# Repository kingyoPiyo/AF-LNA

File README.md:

# AF-LNA
ADA4522-2ARMZ を 4パラで使用した低周波用のローノイズアンプです。  
帯域は 0.1～1000Hz、ゲインは 60dB、ノイズは 5nV/√Hz 以下となるように設計しています。  
⇒ 実測で 3.2nV/√Hz 程度となりました

## 主な仕様
| 項目 | 仕様 |
| ---- | ---- |
| 電源電圧 | 5V±0.5V（USB-C端子より供給） |
| 消費電流 | 50mA 以下 |
| 電圧利得 | 60dB（1000倍） |
| 電圧利得周波数特性 | 0.1～1000Hz（-3dB） |
| 入力換算雑音電圧密度 | 3.2nV/√Hz（typ） at 100Hz |
| 入力電圧範囲 | 入力保護クランプ ±0.5Vpp、DC 重畳は +30V 以下 |
| 入力結合 | AC結合（220uF、有極性コンデンサによる） |
| 入力インピーダンス | 10kΩ at 10～1000Hz |
| 出力インピーダンス | 120Ω at 10～1000Hz |
| 電源構成 | USB-C 側と回路の GND を絶縁型 DCDC により絶縁<br>（絶縁抵抗 100MΩ 以上 at DC500V） |
| 表示LED | 通電表示（D7：緑色）、出力クリッピング表示（D6：赤色） |

## PCB Image  

## Schematic
[Schematic.pdf](doc/schematic.pdf "Schematic")

## 開発環境
- KiCad Version 6.0.5

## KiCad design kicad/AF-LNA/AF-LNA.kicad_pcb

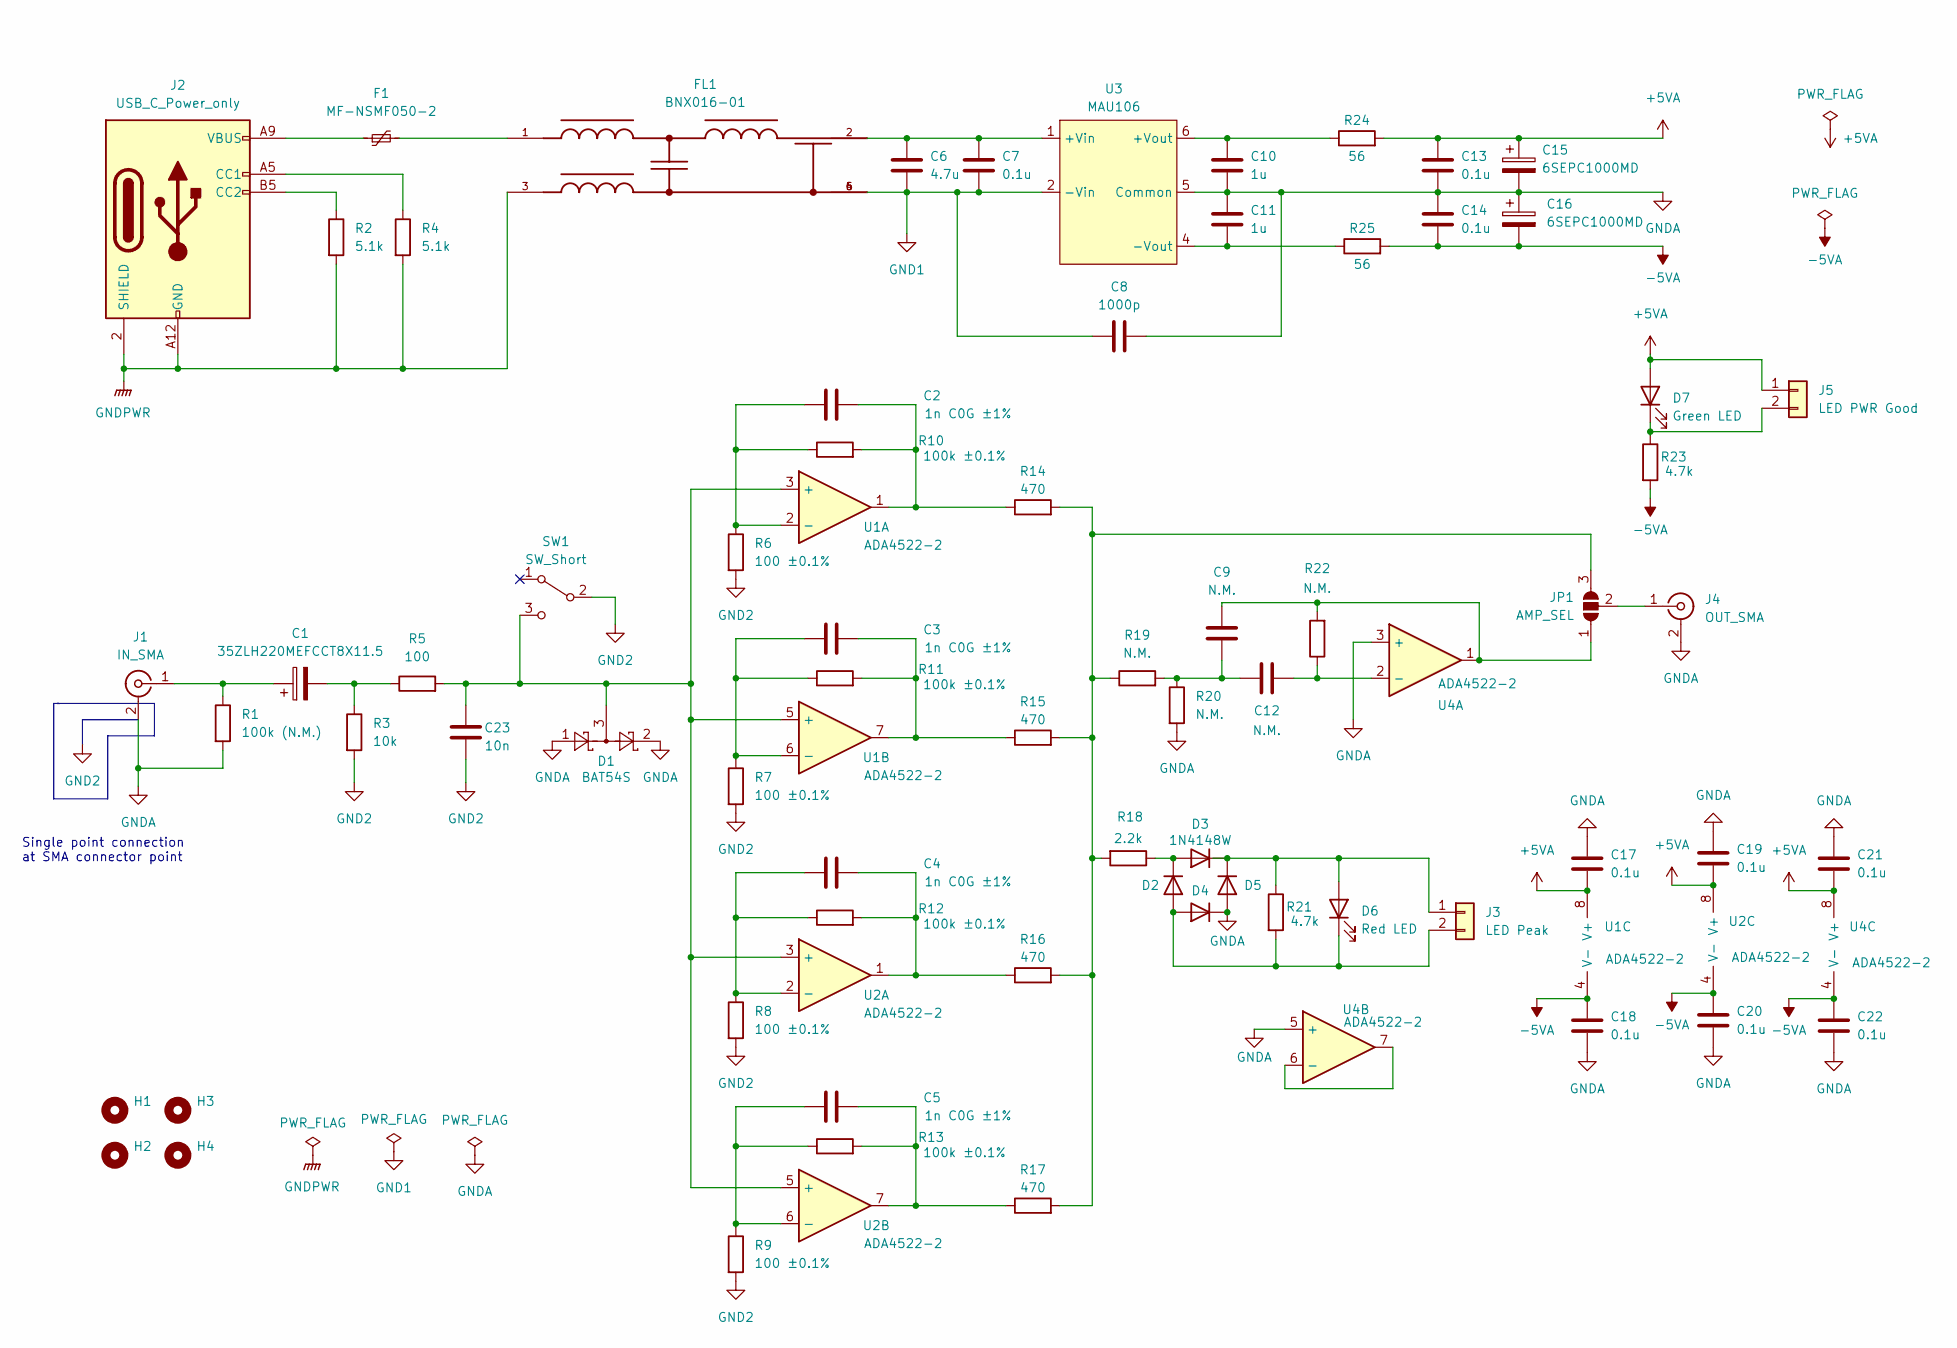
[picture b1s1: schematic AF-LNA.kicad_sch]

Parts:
C1: 35ZLH220MEFCCT8X11.5; CP_Radial_D8.0mm_P3.50mm
C2, C3, C4, C5: 1n C0G ±1%; C_0402_1005Metric
C6: 4.7u; C_0603_1608Metric
C7, C13, C14, C17, C18, C19, C20, C21, C22: 0.1u; C_0603_1608Metric
C8: 1000p; C_1812_4532Metric
C9, C12: N.M.; C_0603_1608Metric
C10, C11: 1u; C_0603_1608Metric
C15, C16: 6SEPC1000MD; CP_Radial_D8.0mm_P3.50mm
C23: 10n; C_0603_1608Metric
D1: BAT54S; SOT-523
D2, D3, D4, D5: 1N4148W; D_SOD-123
D6: Red LED; LED_0603_1608Metric
D7: Green LED; LED_0603_1608Metric
F1: MF-NSMF050-2; Fuse_1206_3216Metric
FL1: BNX016-01; FIL_BNX016-01
H1, H2, H3, H4: MountingHole; MountingHole_3.2mm_M3
J1: IN_SMA; S-063-49-TGG
J2: USB_C_Power_only; USB-C_Power_only
J3: LED Peak; PinHeader_1x02_P2.54mm_Vertical
J4: OUT_SMA; S-063-49-TGG
J5: LED PWR Good; PinHeader_1x02_P2.54mm_Vertical
JP1: AMP_SEL; SolderJumper-3_P1.3mm_Open_RoundedPad1.0x1.5mm
R1: 100k (N.M.); R_0603_1608Metric
R2, R4: 5.1k; R_0603_1608Metric
R3: 10k; R_0603_1608Metric
R5: 100; R_0603_1608Metric
R6, R7, R8, R9: 100 ±0.1%; R_0603_1608Metric
R10, R11, R12, R13: 100k ±0.1%; R_0603_1608Metric
R14, R15, R16, R17: 470; R_0603_1608Metric
R18: 2.2k; R_0603_1608Metric
R19, R20, R22: N.M.; R_0603_1608Metric
R21, R23: 4.7k; R_0603_1608Metric
R24, R25: 56; R_0603_1608Metric
SW1: SW_Short; 2MS1-T1-B4-VS2-Q-E-S
U1, U2, U4: ADA4522-2; MSOP-8_3x3mm_P0.65mm
U3: MAU106

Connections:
+5VA: C13.1, C15.1, C17.2, C19.2, C21.2, D7.2 (A), J5.1, R24.2, U1.8 (V+), U2.8 (V+), U4.8 (V+)
-5VA: C14.2, C16.2, C18.1, C20.1, C22.1, R23.2, R25.2, U1.4 (V-), U2.4 (V-), U4.4 (V-)
GND1: C6.2, C7.2, C8.1, FL1.4, FL1.5, FL1.6, U3.2 (-Vin)
GND2: C23.1, R3.2, R6.2, R7.2, R8.2, R9.2, SW1.2 (B)
GNDA: C8.2, C10.2, C11.1, C13.2, C14.1, C15.2, C16.1, C17.1, C18.2, C19.1, C20.2, C21.1, C22.2, D1.1, D1.2, D4.1 (K), D5.2 (A), J1.2 (Ext), J4.2 (Ext), R1.2, R20.2, U3.5 (Common), U4.3 (+), U4.5 (+)
GNDPWR: FL1.3, J2.2 (SHIELD), J2.A12 (GND), J2.B12 (GND), R2.2, R4.2
unnamed: C1.1, J1.1 (In), R1.1
unnamed: C1.2, R3.1, R5.1
unnamed: C2.1, R6.1, R10.1, U1.2 (-)
unnamed: C2.2, R10.2, R14.1, U1.1
unnamed: C3.1, R7.1, R11.1, U1.6 (-)
unnamed: C3.2, R11.2, R15.1, U1.7
unnamed: C4.1, R8.1, R12.1, U2.2 (-)
unnamed: C4.2, R12.2, R16.1, U2.1
unnamed: C5.1, R9.1, R13.1, U2.6 (-)
unnamed: C5.2, R13.2, R17.1, U2.7
unnamed: C6.1, C7.1, FL1.2, U3.1 (+Vin)
unnamed: C9.1, JP1.1 (A), R22.2, U4.1
unnamed: C10.1, R24.1, U3.6 (+Vout)
unnamed: C11.2, R25.1, U3.4 (-Vout)
unnamed: C9.2, C12.1, R19.2, R20.1
unnamed: C12.2, R22.1, U4.2 (-)
unnamed: D2.1 (K), D3.2 (A), R18.1
unnamed: D2.2 (A), D4.2 (A), D6.1 (K), J3.2, R21.2
unnamed: D3.1 (K), D5.1 (K), D6.2 (A), J3.1, R21.1
unnamed: F1.1, J2.A9 (VBUS), J2.B9 (VBUS)
unnamed: F1.2, FL1.1
unnamed: J2.A5 (CC1), R4.1
unnamed: J2.B5 (CC2), R2.1
unnamed: J4.1 (In), JP1.2 (C)
unnamed: D7.1 (K), J5.2, R23.1
unnamed: JP1.3 (B), R14.2, R15.2, R16.2, R17.2, R18.2, R19.1
unnamed: C23.2, D1.3, R5.2, SW1.3 (C), U1.3 (+), U1.5 (+), U2.3 (+), U2.5 (+)
unnamed: U4.6 (-), U4.7

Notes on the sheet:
Single point connection at SMA connector point

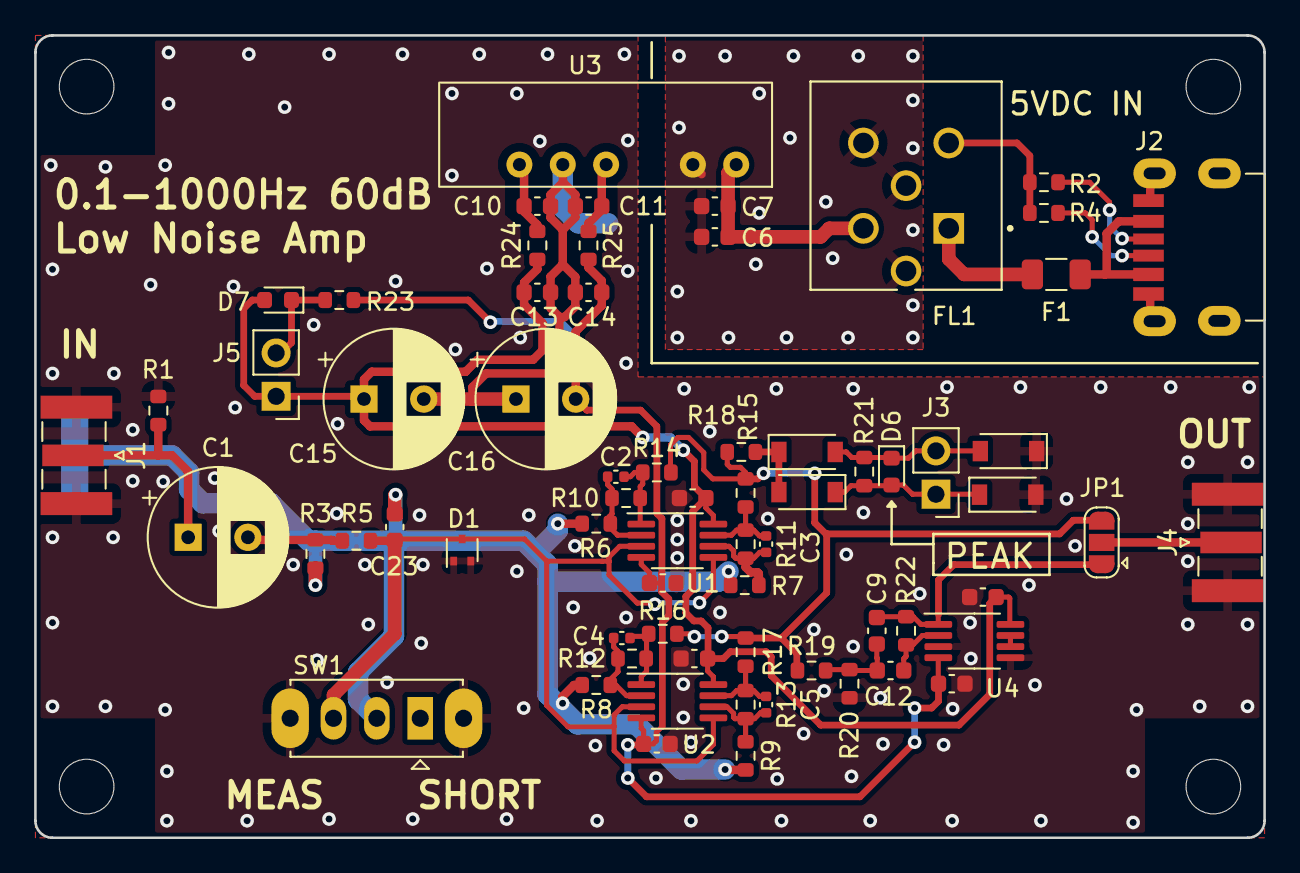
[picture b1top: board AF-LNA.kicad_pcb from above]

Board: 2 copper layers, 72.0 x 47.0 mm, 72 parts (1 on the bottom side), 34 nets.

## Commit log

2022-06-04 Add some files
2022-06-05 Update....
2022-06-05 Update...
2022-06-28 Add pic
2022-07-03 Update Rev1.1
    SW1位置変更、帰還抵抗GND配線をIN側SMA端子から取るように変更
